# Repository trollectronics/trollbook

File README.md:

# Trollbook
*Homebrew 68040 palmtop computer* (http://h4xxel.org/electronics/trollbook/)

This is a work-in-progress palmtop (ish) sized clamshell laptop that we've been
working on for a while.

In its current state, it boots up into a BIOS menu capable of doing
a few simple things like browsing a FAT formatted SD-card, flashing its bootrom
from SD-card and excuting programs from SD-card.
One of the included demo programs can play .MOD music files from SD card.

The entire setup uses about 4.3 Watts while running, including
display and backlight.

The hardware specs as of now can be summed up as following:

 - Motorola 68040FE33V CPU, running at 33 MHz
 - Altera Flex10KA FPGA for glue logic and peripherals (video, uart, spi, audio etc.)
 - Atmel attiny48 for scanning keyboard matrix and mouse, interfacing to I2C peripherals
 - 512 kB of SRAM (used for frame buffer, sound buffer and stage 2 BIOS code)
 - 64 MB of SDRAM
 - 800x480 resolution 7" TFT display, driven at 256 colors (from a 16-bpp palette)
 - Stereo audio DAC, 8 bit/channel, samplerate of 48 kHz
 - SD card interface over SPI
 - On-board SPI Flash ROM (512 kB) for BIOS code
 - 7.4 V, 2.2 Ah battery pack with custom balancing circuitry (which sucks)

The (blue) mainboard is a 10x10 cm 4-layer board, designed by us and manufactured by a Chinese PCB fab.
The larger upper board is a CNC milled peripheral board sporting the keyboard, mouse, IO ports and power supplies.
We desperately need to make a proper case...

## This repository
This repository contains the following:
 - Hardware schematics and layout (kicad)
   - Current Rev 2 motherboard
   - Peripheral board
 - VHDL code for the glue logic/peripheral controller FPGA
 - Source code
   - Stage 1 boot, resides in a small ROM block in the FPGA
   - Stage 2 bios, resides in the large SPI rom
   - Demo code for feature testing/demonstration

## Companion projects
The following projects have been developed for the system:
 - The m68k-emu system emulator (https://github.com/slaeshjag/m68k-emu)
 - The trollos operating system (https://github.com/h4xxel/trollos)

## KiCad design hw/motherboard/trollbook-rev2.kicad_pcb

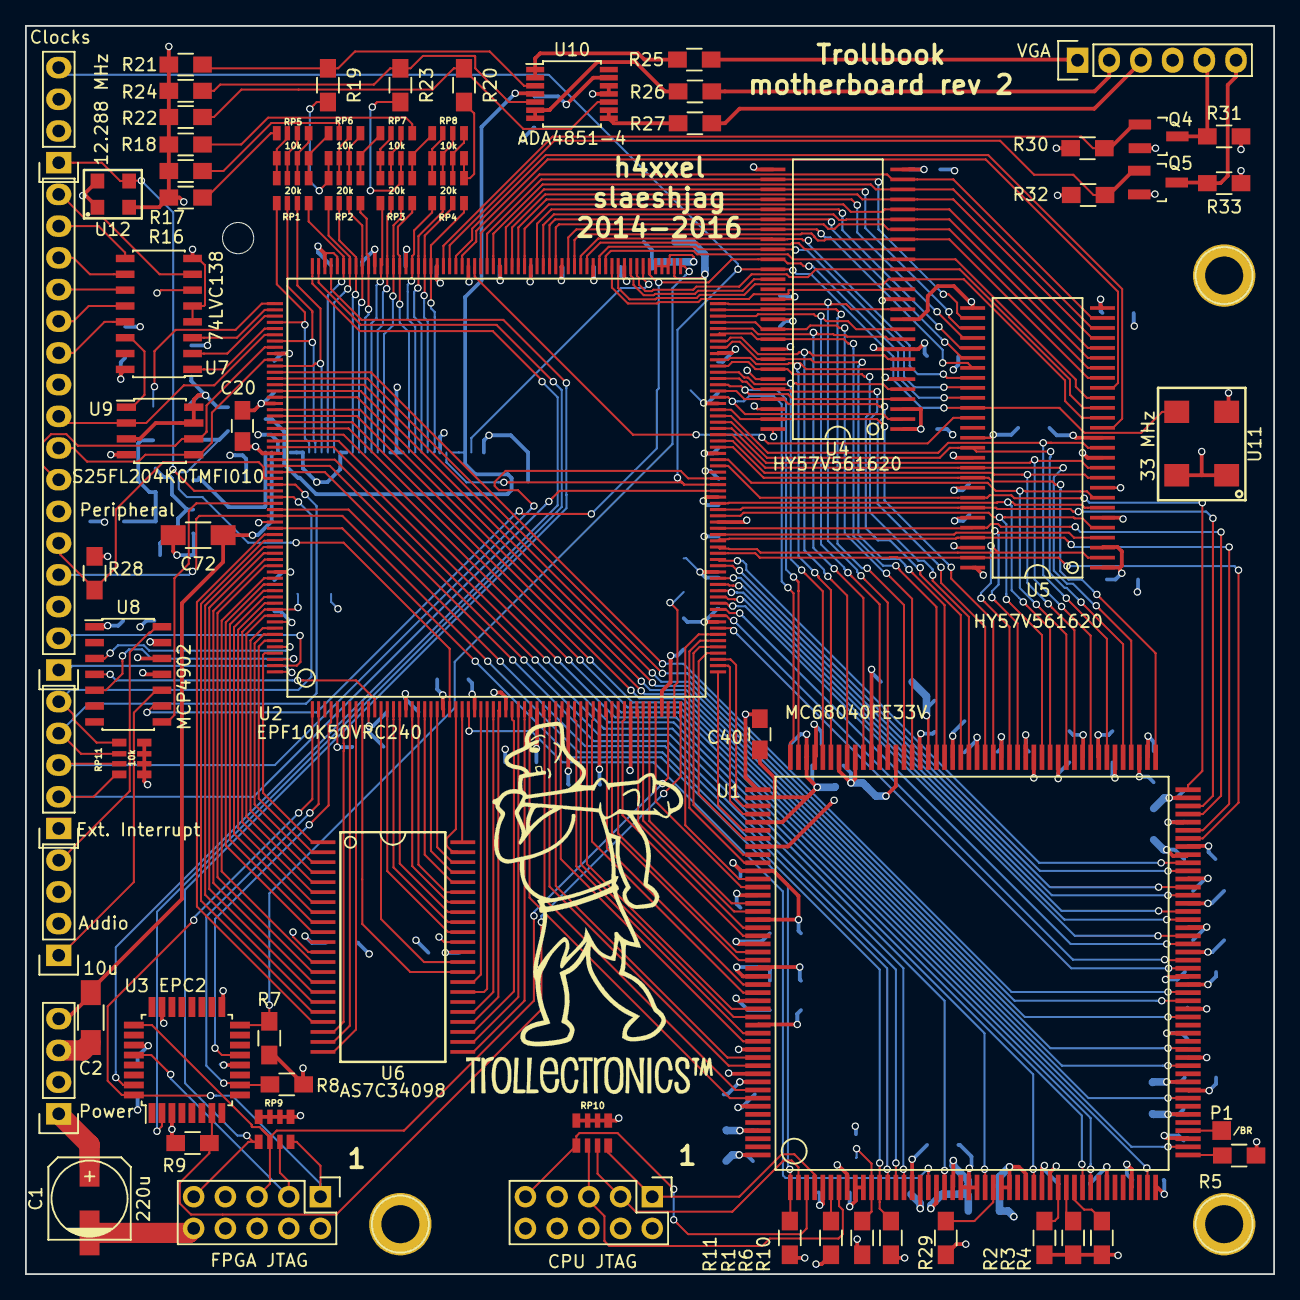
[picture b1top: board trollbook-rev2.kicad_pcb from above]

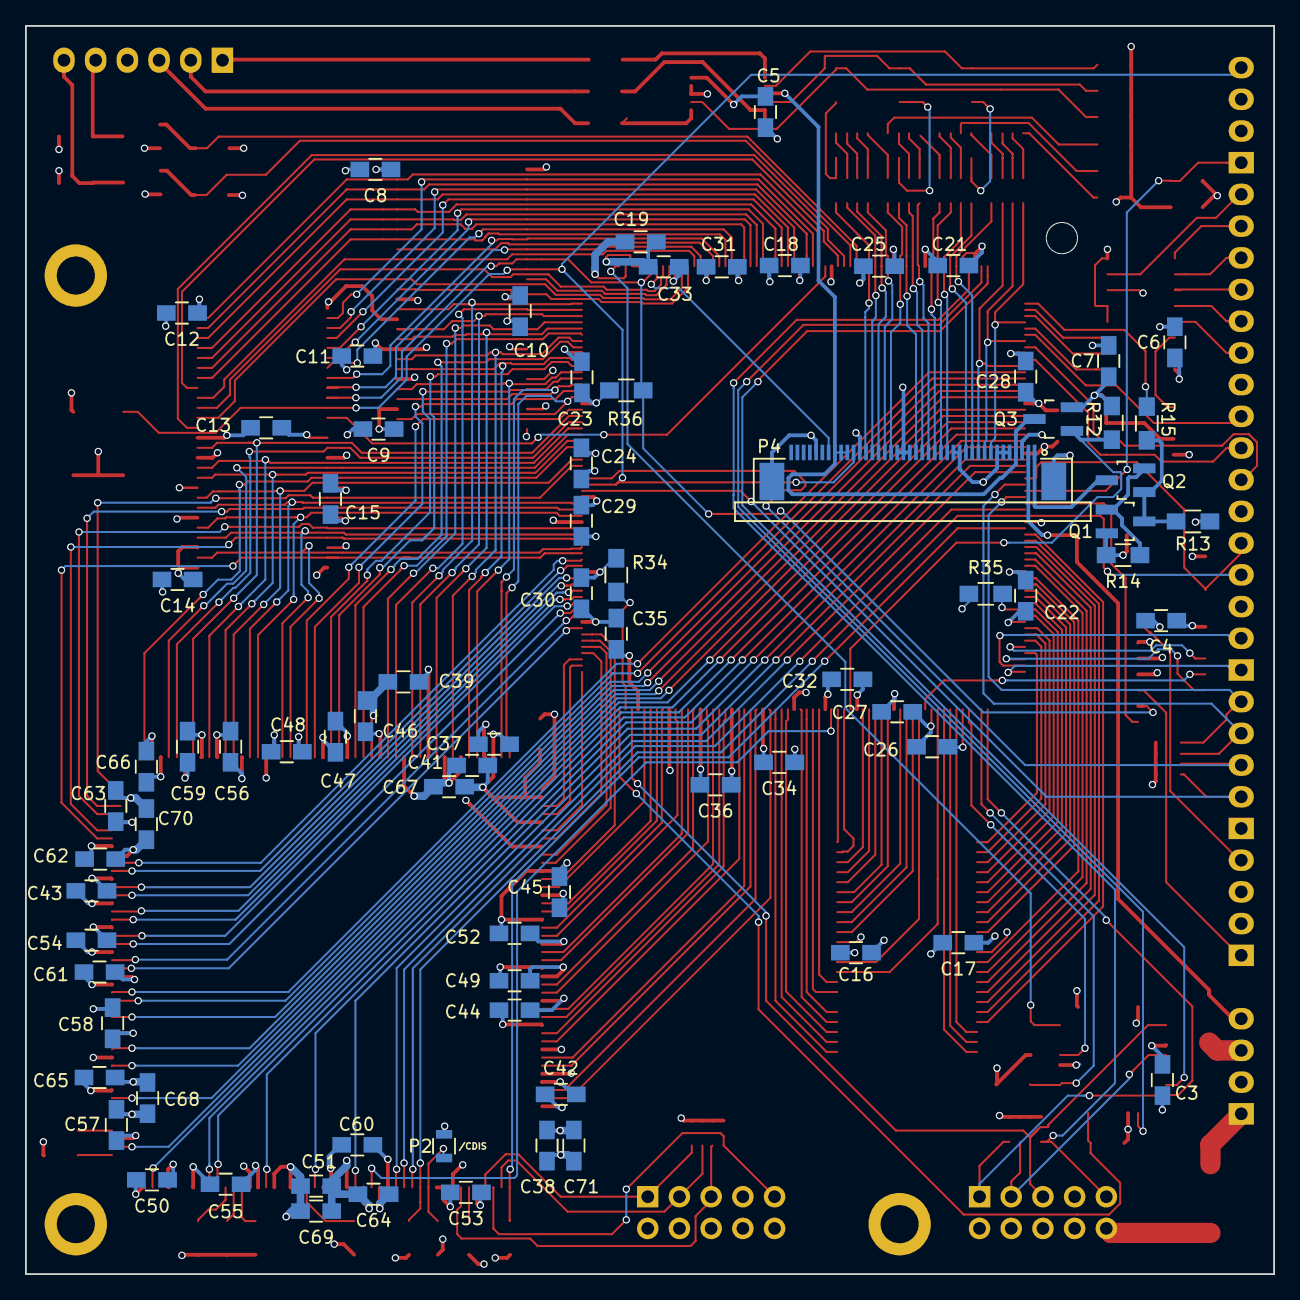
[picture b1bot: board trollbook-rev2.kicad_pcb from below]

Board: 4 copper layers, 100.0 x 100.0 mm, 147 parts (79 on the bottom side), 258 nets.

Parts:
C1: 220u; c_elec_6.3x7.7
C2: 10u; C_1206_HandSoldering
C3, C4, C5, C6, C7, C8, C9, C10, C11, C12, C13, C14, C15, C16, C17, C18, C19, C20, C21, C22, C23, C24, C25, C26, C27, C28, C29, C30, C31, C32, C33, C34, C35, C36, C67, C68, C69, C70, C71: 100n; C_0805_HandSoldering
C37, C38, C39, C40, C41, C42, C43, C44, C45, C46, C47, C48, C49, C50, C51, C52, C53, C54, C55, C56, C57, C58, C59, C60, C61, C62, C63, C64, C65, C66: 10n; C_0805_HandSoldering
C72: 1u; C_1206_HandSoldering
CON1: FPGA JTAG; Pin_Header_Straight_2x05
CON2: CPU JTAG; Pin_Header_Straight_2x05
P1: /BR; Measurement_Point_Square-SMD-Pad_Small
P2: /CDIS; R_0805
P3: Audio; Pin_Header_Straight_1x04
P4: ER-CON40HT-1
P5: Power; Pin_Header_Straight_1x04
P6: Peripheral; Pin_Header_Straight_1x16
P7: VGA; Pin_Header_Straight_1x06
P8: Clocks; Pin_Header_Straight_1x04
P9: Ext. Interrupt; Pin_Header_Straight_1x05
Q1, Q2, Q4, Q5: 2N7002E; SOT-23_Handsoldering
Q3: DMP3030SN-7; SOT-23_Handsoldering
R1, R10, R11, R15, R29, R30, R31, R32, R33: R; R_0805_HandSoldering
R2, R3, R4, R5, R6, R12, R16, R17, R18, R34, R35, R36: 10k; R_0805_HandSoldering
R7, R8, R9, R28: 1k; R_0805_HandSoldering
R13: 470k; R_0805_HandSoldering
R14: 20R; R_0805_HandSoldering
R19, R20, R23: 560k; R_0805_HandSoldering
R21, R22, R24: 180k; R_0805_HandSoldering
R25, R26, R27: 75; R_0805_HandSoldering
RP1, RP2, RP3, RP4: 20k; RPACK8_SMD
RP5, RP6, RP7, RP8, RP9, RP10, RP11: 10k; RPACK8_SMD
U1: MC68040FE33V; QFP-184
U2: EPF10K50VRC240; RQFP-240
U3: EPC2; TQFP-32_7x7mm_Pitch0.8mm
U4, U5: HY57V561620; TSOP54
U6: AS7C34098; TSOP44
U7: 74LVC138; SOIC-16_3.9x9.9mm_Pitch1.27mm
U8: MCP4902; SOIC-14_3.9x8.7mm_Pitch1.27mm
U9: S25FL204K0TMFI010; SOIC-8_3.9x4.9mm_Pitch1.27mm
U10: ADA4851-4; TSSOP-14_4.4x5mm_Pitch0.65mm
U11: 33 MHz; OSC-VCC1-B3B
U12: 12.288 MHz; OSC-ASFLMB

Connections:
+3V3: C1.1, C3.1, C4.1, C5.1, C6.1, C7.1, C8.1, C9.1, C10.1, C11.1, C12.1, C13.1, C14.1, C15.1, C16.1, C17.1, C18.1, C19.1, C20.1, C21.1, C22.1, C23.2, C24.2, C25.2, C26.2, C27.2, C28.1, C29.1, C30.1, C31.1, C32.1, C33.2, C34.2, C35.2, C36.2, C37.1, C38.1, C39.1, C40.1, C41.1, C42.2, C43.2, C44.2, C45.2, C46.2, C47.1, C48.1, C49.1, C50.1, C51.1, C52.2, C53.2, C54.2, C55.2, C56.2, C57.1, C58.1, C59.1, C60.1, C61.1, C62.2, C63.2, C64.2, C65.2, C66.2, C67.1, C68.1, C69.1, C70.1, C71.1, CON1.4, CON2.4, P5.1, Q3.2, R5.1, R6.2, R7.1, R8.1, R9.1, R11.1, R15.1, R29.1, R30.2, R31.2, R32.2, R33.2, R34.1, R35.1, RP9.1, RP9.2, RP9.3, RP9.4, RP10.1, RP10.2, RP10.3, RP10.4, RP11.1, RP11.2, RP11.3, RP11.4, U1.9, U1.10, U1.16, U1.19, U1.21, U1.32, U1.43, U1.49, U1.56, U1.62, U1.69, U1.75, U1.81, U1.84, U1.88, U1.94, U1.100, U1.102, U1.109, U1.115, U1.122, U1.128, U1.136, U1.140, U1.143, U1.149, U1.155, U1.161, U1.168, U1.175, U1.181, U2.5, U2.16, U2.27, U2.37, U2.47, U2.57, U2.77, U2.89, U2.96, U2.112, U2.122, U2.130, U2.140, U2.150, U2.160, U2.170, U2.189, U2.205, U2.224, U3.3, U3.17, U3.23, U3.27, U4.1, U4.3, U4.9, U4.14, U4.27, U4.43, U4.49, U5.1, U5.3, U5.9, U5.14, U5.27, U5.43, U5.49, U6.11, U6.33, U7.6, U7.16, U8.1, U8.11, U8.13, U9.3, U9.7, U9.8, U10.13, U11.1, U11.4, U12.1, U12.4
/A0: U1.70, U2.68
/A1: U1.71, U2.70
/A2: U1.73, U2.71
/A3: U1.74, U2.72
/A4: U1.76, U2.73
/A5: U1.77, U2.74
/A6: U1.79, U2.75
/A7: U1.80, U2.76
/A8: U1.82, U2.78
/A9: U1.83, U2.79
/A10: U1.173, U2.39
/A11: U1.172, U2.40
/A12: U1.170, U2.41
/A13: U1.169, U2.43
/A14: U1.167, U2.44
/A15: U1.166, U2.45
/A16: U1.164, U2.46
/A17: U1.163, U2.48
/A18: U1.160, U2.49
/A19: U1.159, U2.50
/A20: U1.157, U2.51
/A21: U1.156, U2.53
/A22: U1.154, U2.54
/A23: U1.153, U2.55
/A24: U1.151, U2.56
/A25: U1.150, U2.67
/A26: U1.148, U2.66
/A27: U1.147, U2.65
/A28: U1.145, U2.64
/A29: U1.144, U2.61
/A30: U1.142, U2.62
/A31: U1.141, U2.63
/AUDIOL: P3.4, U8.14
/AUDIOR: P3.1, U8.10
/CLK12: P8.1, U2.211, U12.3
/CLK33: P4.30, P8.4, U2.91, U4.38, U5.38, U11.3
/CONF_CLK: U2.179, U3.2
/CONF_CS: R8.2, U2.2, U3.10
/CONF_DATA: U2.180, U3.31
/CONF_INIT: R7.2, U2.121, U3.16
/CONF_OE: R9.2, U2.60, U3.7
/CONF_TDO: CON1.3, RP9.7, U3.28
/CPUBB: R5.2, U1.47
/CPUBG: R4.2, U1.36
/CPUBR: P1.1, U1.50
/CPUCDIS: P2.1, R6.1, U1.11
/CPUCLK: U1.18, U2.26
/CPUIPL0: U1.15, U2.207
/CPUIPL1: U1.14, U2.208
/CPUIPL2: U1.13, U2.214
/CPULFO: U1.20, U2.206
/CPULOC: R1.2, U1.6
/CPURSTI: P6.4, R10.2, U1.12, U2.215
/CPURSTO: R11.2, U1.1, U2.217
/CPURW: U1.58, U2.196
/CPUSC0: R2.2, U1.34
/CPUSC1: R3.2, U1.35
/CPUSCD: U1.25, U2.204
/CPUSIZ0: U1.60, U2.195
/CPUSIZ1: U1.54, U2.198
/CPUTA: U1.38, U2.201
/CPUTBI: U1.31, U2.203
/CPUTCK: CON2.1, RP10.8, U1.4
/CPUTDI: CON2.9, RP10.5, U1.3
/CPUTDO: CON2.3, RP10.7, U1.2
/CPUTEA: U1.37, U2.202
/CPUTIP: U1.45, U2.200
/CPUTM0: U1.64, U2.194
/CPUTM1: U1.66, U2.193
/CPUTM2: U1.67, U2.192
/CPUTMS: CON2.5, RP10.6, U1.7
/CPUTP: U1.48, U2.199
/CPUTT0: U1.177, U2.36
/CPUTT1: U1.176, U2.38
/D0: U1.138, U2.105, U4.2
/D1: U1.137, U2.107, U4.4
/D2: U1.134, U2.109, U4.5
/D3: U1.133, U2.111, U4.7
/D4: U1.131, U2.114, U4.8
/D5: U1.129, U2.116, U4.10
/D6: U1.127, U2.118, U4.11
/D7: U1.126, U2.120, U4.13
/D8: U1.124, U2.119, U4.42
/D9: U1.123, U2.117, U4.44
/D10: U1.120, U2.115, U4.45
/D11: U1.119, U2.113, U4.47
/D12: U1.117, U2.110, U4.48
/D13: U1.116, U2.108, U4.50
/D14: U1.114, U2.106, U4.51
/D15: U1.113, U2.103, U4.53
/D16: U1.111, U2.81, U5.2
/D17: U1.110, U2.83, U5.4
/D18: U1.107, U2.86, U5.5
/D19: U1.106, U2.88, U5.7
/D20: U1.104, U2.95, U5.8
/D21: U1.103, U2.98, U5.10
/D22: U1.101, U2.100, U5.11
/D23: U1.99, U2.102, U5.13
/D24: U1.97, U2.101, U5.42
/D25: U1.96, U2.99, U5.44
/D26: U1.93, U2.97, U5.45
/D27: U1.92, U2.94, U5.47
/D28: U1.90, U2.87, U5.48
/D29: U1.89, U2.84, U5.50
/D30: U1.87, U2.82, U5.51
/D31: U1.86, U2.80, U5.53
/EXTINT0: P9.2, RP11.8, U2.90
/EXTINT1: P9.3, RP11.7, U2.92
/EXTINT2: P9.4, RP11.6, U2.210
/EXTINT3: P9.5, RP11.5, U2.212
/FPGA_TCK: CON1.1, RP9.8, U2.1, U3.32
/FPGA_TDI: CON1.9, RP9.5, U2.177
/FPGA_TDO: U2.4, U3.13
/FPGA_TMS: CON1.5, RP9.6, U2.58, U3.25
/LLA1: U2.237, U6.1
/LLA2: U2.235, U6.2
/LLA3: U2.234, U6.3
/LLA4: U2.233, U6.4
/LLA5: U2.231, U6.5
/LLA6: U2.219, U6.18
/LLA7: U2.218, U6.19
/LLA8: U2.6, U6.20
/LLA9: U2.7, U6.21
/LLA10: U2.8, U6.22
/LLA11: U2.35, U6.23
/LLA12: U2.34, U6.24
/LLA13: U2.33, U6.25
/LLA14: U2.31, U6.26
/LLA15: U2.30, U6.27
/LLA16: U2.21, U6.42
/LLA17: U2.24, U6.43
/LLA18: U2.25, U6.44
/LLCE: R35.2, U2.230, U6.6
/LLD0: U2.229, U6.7
/LLD1: U2.228, U6.8
/LLD2: U2.227, U6.9
/LLD3: U2.226, U6.10
/LLD4: U2.225, U6.13
/LLD5: U2.223, U6.14
/LLD6: U2.222, U6.15
/LLD7: U2.221, U6.16
/LLD8: U2.29, U6.29
/LLD9: U2.28, U6.30
/LLD10: U2.9, U6.31
/LLD11: U2.12, U6.32
/LLD12: U2.13, U6.35
/LLD13: U2.14, U6.36
/LLD14: U2.15, U6.37
/LLD15: U2.17, U6.38
/LLLB: U2.18, U6.39
/LLOE: U2.20, U6.41
/LLUB: U2.19, U6.40
/LLWE: U2.220, U6.17
/PWRON_RESET: P6.5, R28.1, U2.209
/RAM0CS: U2.136, U4.19
/RAM0LDQM: U2.132, U4.15
/RAM0UDQM: U2.129, U4.39
/RAM1CS: U2.156, U5.19
/RAM1LDQM: U2.157, U5.15
/RAM1UDQM: U2.154, U5.39
/RAMA0: U2.146, U4.23, U5.23
/RAMA1: U2.148, U4.24, U5.24
/RAMA2: U2.151, U4.25, U5.25
/RAMA3: U2.153, U4.26, U5.26
/RAMA4: U2.152, U4.29, U5.29
/RAMA5: U2.149, U4.30, U5.30
/RAMA6: U2.147, U4.31, U5.31
/RAMA7: U2.144, U4.32, U5.32
/RAMA8: U2.142, U4.33, U5.33
/RAMA9: U2.139, U4.34, U5.34
/RAMA10: U2.143, U4.22, U5.22
/RAMA11: U2.137, U4.35, U5.35
/RAMA12: U2.134, U4.36, U5.36
/RAMB0: U2.138, U4.20, U5.20
/RAMB1: U2.141, U4.21, U5.21
/RAMCAS: U2.128, U4.17, U5.17
/RAMCKE: R36.1, U2.126, U4.37, U5.37, U8.9
/RAMRAS: U2.133, U4.18, U5.18
/RAMWE: U2.131, U4.16, U5.16
/SNDSYNC: U2.213, U8.8
/SPI0CLK: P6.7, U2.188, U9.6
/SPI0MISO: P6.9, U2.186, U9.2
/SPI0MOSI: P6.8, U2.190, U9.5
/SPI0SS1: U7.14, U9.1
/SPI0SS2: P6.11, U7.13
/SPI0SS3: P6.12, U7.12
/SPI0SS4: P6.13, U7.11
/SPI0SS5: P6.14, U7.10
/SPI0SS6: P6.15, U7.9
/SPI0SS7: P6.16, U7.7
/SPI0SSBIT0: U2.185, U7.1
/SPI0SSBIT1: U2.183, U7.2
/SPI0SSBIT2: U2.182, U7.3
/SPI1CLK: U2.11, U8.4
/SPI1MOSI: U2.238, U8.5
/SPI1SS: U2.236, U8.3
/UARTRX: P6.1, U2.240
/UARTTX: P6.2, U2.239
/VGAB0: P4.24, RP3.4, U2.166
/VGAB1: P4.25, RP4.1, U2.164
/VGAB2: P4.26, RP4.2, U2.163
/VGAB3: P4.27, RP4.3, U2.162
/VGAB4: P4.28, RP4.4, U2.161
/VGADEN: P4.34, U2.127
/VGADISP: P4.4, P4.31, P4.32, P4.33, Q3.3, U10.4
/VGAG0: P4.15, RP2.2, U2.173
/VGAG1: P4.16, RP2.3, U2.172
/VGAG2: P4.17, RP2.4, U2.171
/VGAG3: P4.18, RP3.1, U2.169
/VGAG4: P4.19, RP3.2, U2.168
/VGAG5: P4.20, RP3.3, U2.167
/VGAHSYNC: Q4.1, R30.1, U2.159
/VGALED_ANODE: C2.1, C72.1, P4.2, P5.4
/VGALED_CATHODE: P4.1, Q2.3
/VGALED_PWM: R12.2, U2.181
/VGAPWR: Q3.1, R15.2, U2.23
/VGAR0: P4.8, RP1.1, U2.184
/VGAR1: P4.9, RP1.2, U2.187
/VGAR2: P4.10, RP1.3, U2.191
/VGAR3: P4.11, RP1.4, U2.175
/VGAR4: P4.12, RP2.1, U2.174
/VGAVSYNC: Q5.1, R32.1, U2.158
GND: C1.2, C2.2, C3.2, C4.2, C5.2, C6.2, C7.2, C8.2, C9.2, C10.2, C11.2, C12.2, C13.2, C14.2, C15.2, C16.2, C17.2, C18.2, C19.2, C20.2, C21.2, C22.2, C23.1, C24.1, C25.1, C26.1, C27.1, C28.2, C29.2, C30.2, C31.2, C32.2, C33.1, C34.1, C35.1, C36.1, C37.2, C38.2, C39.2, C40.2, C41.2, C42.1, C43.1, C44.1, C45.1, C46.1, C47.2, C48.2, C49.2, C50.2, C51.2, C52.1, C53.1, C54.1, C55.1, C56.1, C57.2, C58.2, C59.2, C60.2, C61.2, C62.1, C63.1, C64.1, C65.1, C66.1, C67.2, C68.2, C69.2, C70.2, C71.2, C72.2, CON1.2, CON1.10, CON2.2, CON2.10, P2.2, P3.2, P3.3, P4.3, P4.5, P4.6, P4.7, P4.13, P4.14, P4.21, P4.22, P4.23, P4.29, P4.36, P4.GND, P5.2, P5.3, P6.3, P6.6, P6.10, P7.4, P8.2, P8.3, P9.1, Q1.2, Q4.2, Q5.2, R1.1, R2.1, R3.1, R4.1, R10.1, R13.2, R14.2, R16.1, R17.1, R18.1, R21.2, R22.2, R24.2, R28.2, R36.2, U1.5, U1.8, U1.17, U1.22, U1.23, U1.24, U1.27, U1.28, U1.30, U1.33, U1.40, U1.46, U1.52, U1.55, U1.59, U1.65, U1.68, U1.72, U1.78, U1.85, U1.91, U1.95, U1.98, U1.105, U1.108, U1.112, U1.118, U1.121, U1.125, U1.130, U1.132, U1.135, U1.139, U1.146, U1.152, U1.158, U1.162, U1.165, U1.171, U1.174, U1.178, U1.184, U2.10, U2.22, U2.32, U2.42, U2.52, U2.69, U2.85, U2.93, U2.104, U2.123, U2.124, U2.125, U2.135, U2.145, U2.155, U2.165, U2.176, U2.178, U2.197, U2.216, U2.232, U3.12, U4.6, U4.12, U4.28, U4.41, U4.46, U4.52, U4.54, U5.6, U5.12, U5.28, U5.41, U5.46, U5.52, U5.54, U6.12, U6.34, U7.4, U7.5, U7.8, U8.12, U9.4, U10.11, U10.12, U11.2, U12.2
unnamed: P7.1, R25.1
unnamed: P7.2, R26.1
unnamed: P7.3, R27.1
unnamed: P7.5, Q4.3, R31.1
unnamed: P7.6, Q5.3, R33.1
unnamed: Q1.1, Q2.2, R14.1
unnamed: Q1.3, Q2.1, R12.1, R13.1
unnamed: R16.2, RP5.8
unnamed: R17.2, RP6.7
unnamed: R18.2, RP7.5
unnamed: R19.1, R21.1, U10.3
unnamed: R19.2, RP2.8, RP6.1
unnamed: R20.1, R22.1, U10.10
unnamed: R20.2, RP4.5, RP8.4
unnamed: R23.1, R24.1, U10.5
unnamed: R23.2, RP3.6, RP7.3
unnamed: R25.2, U10.1, U10.2
unnamed: R26.2, U10.6, U10.7
unnamed: R27.2, U10.8, U10.9
unnamed: R29.2, U1.26
unnamed: R34.2, U2.59
unnamed: RP1.5, RP5.4, RP6.8
unnamed: RP1.6, RP5.3, RP5.5
unnamed: RP1.7, RP5.2, RP5.6
unnamed: RP1.8, RP5.1, RP5.7
unnamed: RP2.5, RP6.4, RP7.8
unnamed: RP2.6, RP6.3, RP6.5
unnamed: RP2.7, RP6.2, RP6.6
unnamed: RP3.5, RP7.4, RP8.8
unnamed: RP3.7, RP7.2, RP7.6
unnamed: RP3.8, RP7.1, RP7.7
unnamed: RP4.6, RP8.3, RP8.5
unnamed: RP4.7, RP8.2, RP8.6
unnamed: RP4.8, RP8.1, RP8.7

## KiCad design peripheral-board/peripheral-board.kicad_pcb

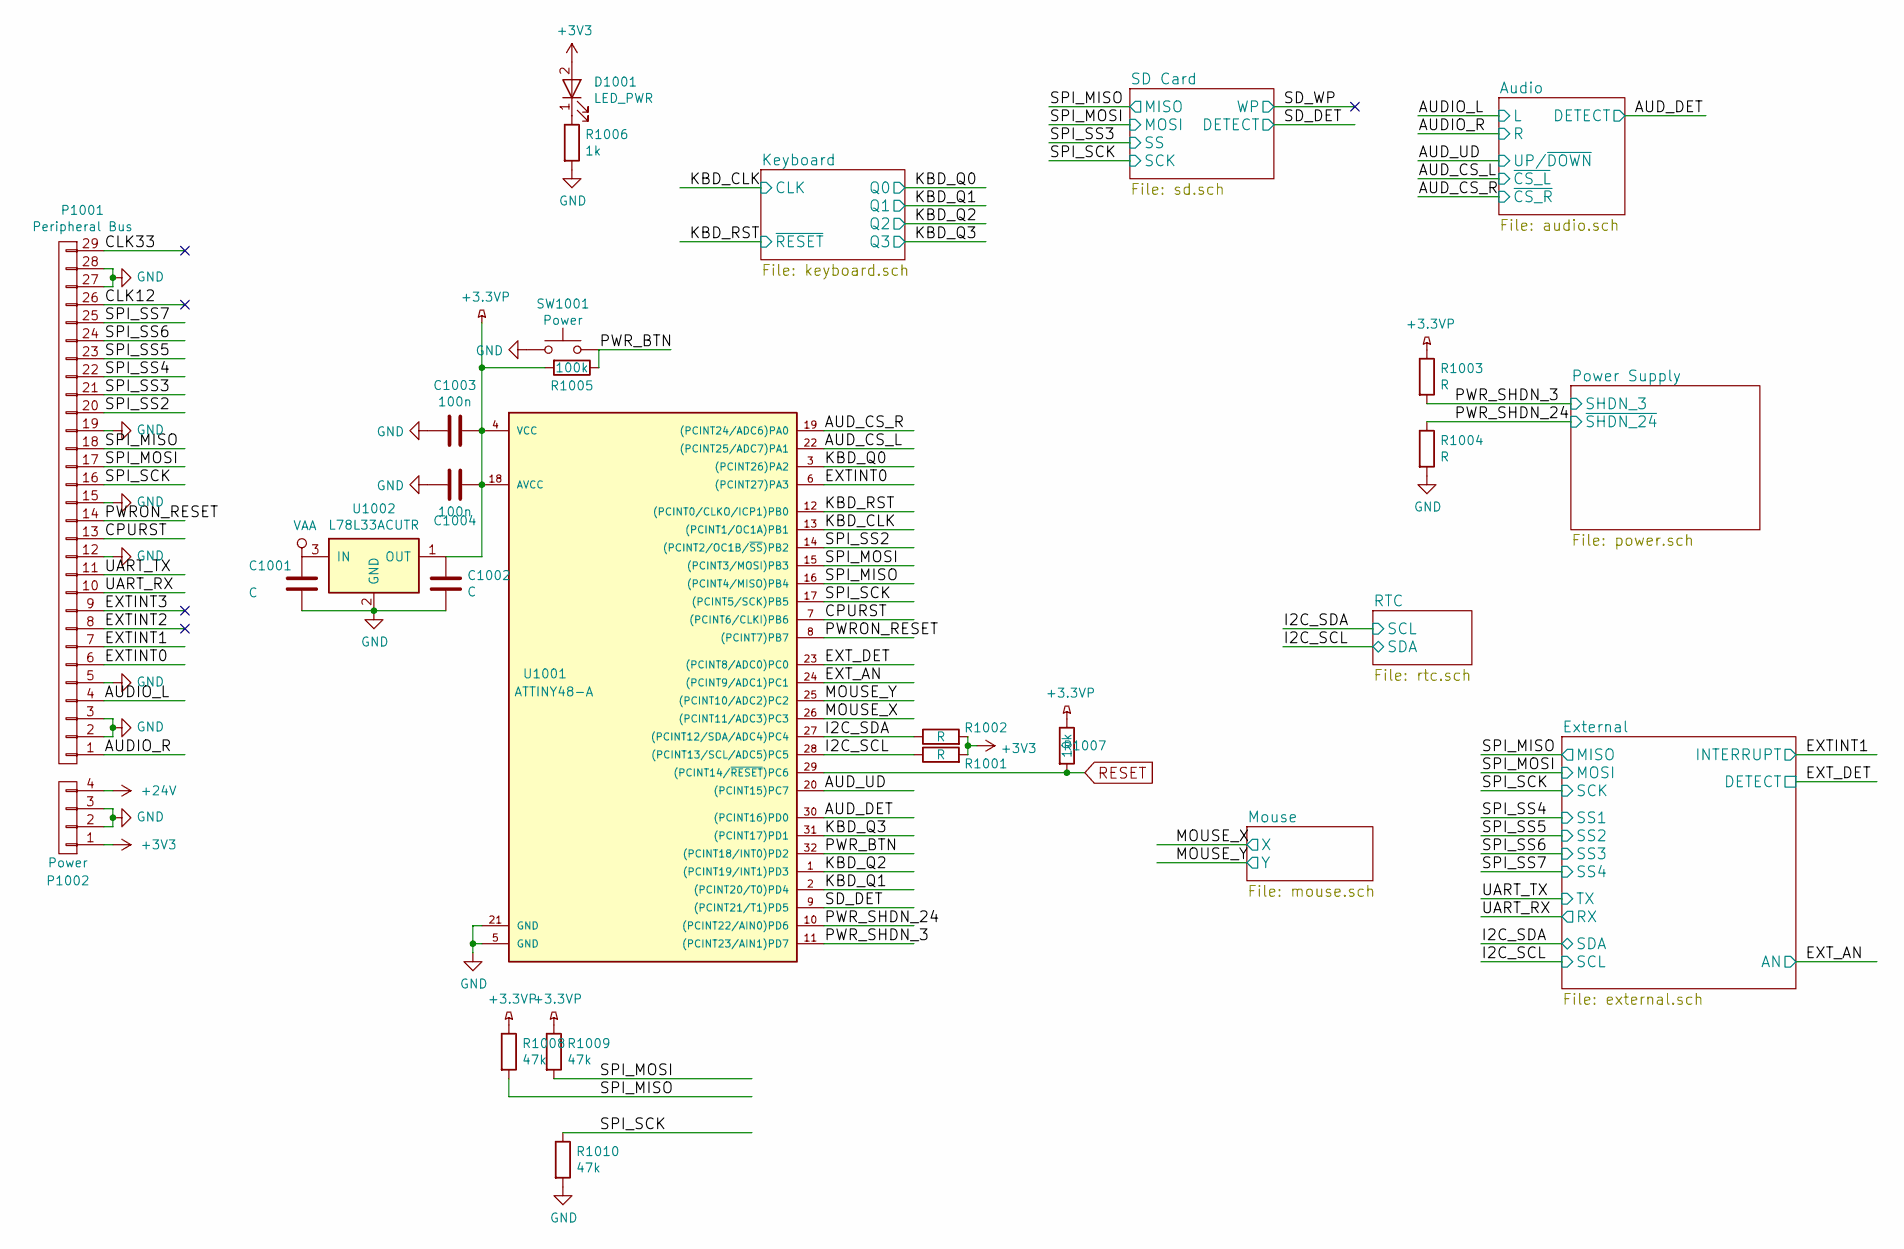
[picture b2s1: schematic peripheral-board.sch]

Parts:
C1001, C1002: C; C_0805
C1003, C1004: 100n; C_0805
D1001: LED_PWR; LED-3MM
P1001: Peripheral Bus; Socket_Strip_Straight_1x29
P1002: Power; Socket_Strip_Straight_1x04
R1001, R1002, R1003, R1004: R; R_0805
R1005: 100k; R_0805
R1006: 1k; R_0805
R1007: 10k; R_0805
R1008, R1009, R1010: 47k; R_0805
SW1001: Power; SMD-TACT-5.2x5.2x2mm
U1001: ATTINY48-A; TQFP-32_7x7mm_Pitch0.8mm
U1002: L78L33ACUTR; SOT89-3_Housing

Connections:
+3.3VP: C1002.1, C1003.1, C1004.1, R1003.1, R1005.2, R1007.1, R1008.1, R1009.1, U1001.4 (VCC), U1001.18 (AVCC), U1002.1 (OUT); also elsewhere on the board
+3V3: D1001.2 (A), P1002.1, R1001.2, R1002.2; also elsewhere on the board
+24V: P1002.4; also elsewhere on the board
/AUDIO_L: P1001.4; also elsewhere on the board
/AUDIO_R: P1001.1; also elsewhere on the board
/AUD_CS_L: U1001.22 ((PCINT25/ADC7)PA1); also elsewhere on the board
/AUD_CS_R: U1001.19 ((PCINT24/ADC6)PA0); also elsewhere on the board
/AUD_DET: U1001.30 ((PCINT16)PD0); also elsewhere on the board
/AUD_UD: U1001.20 ((PCINT15)PC7); also elsewhere on the board
/CLK12: P1001.26
/CLK33: P1001.29
/CPURST: P1001.13, U1001.7 ((PCINT6/CLKI)PB6)
/EXTINT0: P1001.6, U1001.6 ((PCINT27)PA3)
/EXTINT1: P1001.7; also elsewhere on the board
/EXTINT2: P1001.8
/EXTINT3: P1001.9
/EXT_AN: U1001.24 ((PCINT9/ADC1)PC1); also elsewhere on the board
/EXT_DET: U1001.23 ((PCINT8/ADC0)PC0); also elsewhere on the board
/I2C_SCL: R1001.1, U1001.28 ((PCINT13/SCL/ADC5)PC5); also elsewhere on the board
/I2C_SDA: R1002.1, U1001.27 ((PCINT12/SDA/ADC4)PC4); also elsewhere on the board
/KBD_CLK: U1001.13 ((PCINT1/OC1A)PB1); also elsewhere on the board
/KBD_Q0: U1001.3 ((PCINT26)PA2); also elsewhere on the board
/KBD_Q1: U1001.2 ((PCINT20/T0)PD4); also elsewhere on the board
/KBD_Q2: U1001.1 ((PCINT19/INT1)PD3); also elsewhere on the board
/KBD_Q3: U1001.31 ((PCINT17)PD1); also elsewhere on the board
/KBD_RST: U1001.12 ((PCINT0/CLKO/ICP1)PB0); also elsewhere on the board
/MOUSE_X: U1001.26 ((PCINT11/ADC3)PC3); also elsewhere on the board
/MOUSE_Y: U1001.25 ((PCINT10/ADC2)PC2); also elsewhere on the board
/PWRON_RESET: P1001.14, U1001.8 ((PCINT7)PB7)
/PWR_BTN: R1005.1, SW1001.2, U1001.32 ((PCINT18/INT0)PD2)
/PWR_SHDN_3: R1003.2, U1001.11 ((PCINT23/AIN1)PD7); also elsewhere on the board
/PWR_SHDN_24: R1004.1, U1001.10 ((PCINT22/AIN0)PD6); also elsewhere on the board
/SD_DET: U1001.9 ((PCINT21/T1)PD5); also elsewhere on the board
/SPI_MISO: P1001.18, R1008.2, U1001.16 ((PCINT4/MISO)PB4); also elsewhere on the board
/SPI_MOSI: P1001.17, R1009.2, U1001.15 ((PCINT3/MOSI)PB3); also elsewhere on the board
/SPI_SCK: P1001.16, R1010.1, U1001.17 ((PCINT5/SCK)PB5); also elsewhere on the board
/SPI_SS2: P1001.20, U1001.14 ((PCINT2/OC1B/~SS~)PB2)
/SPI_SS3: P1001.21; also elsewhere on the board
/SPI_SS4: P1001.22; also elsewhere on the board
/SPI_SS5: P1001.23; also elsewhere on the board
/SPI_SS6: P1001.24; also elsewhere on the board
/SPI_SS7: P1001.25; also elsewhere on the board
/UART_RX: P1001.10; also elsewhere on the board
/UART_TX: P1001.11; also elsewhere on the board
GND: C1001.2, C1002.2, C1003.2, C1004.2, P1001.2, P1001.3, P1001.5, P1001.12, P1001.15, P1001.19, P1001.27, P1001.28, P1002.2, P1002.3, R1004.2, R1006.2, R1010.2, SW1001.1, U1001.5 (GND), U1001.21 (GND), U1002.2 (GND); also elsewhere on the board
unnamed: D1001.1 (K), R1006.1
RESET: R1007.2, U1001.29 ((PCINT14/~RESET~)PC6); also elsewhere on the board
VAA: C1001.1, U1002.3 (IN); also elsewhere on the board

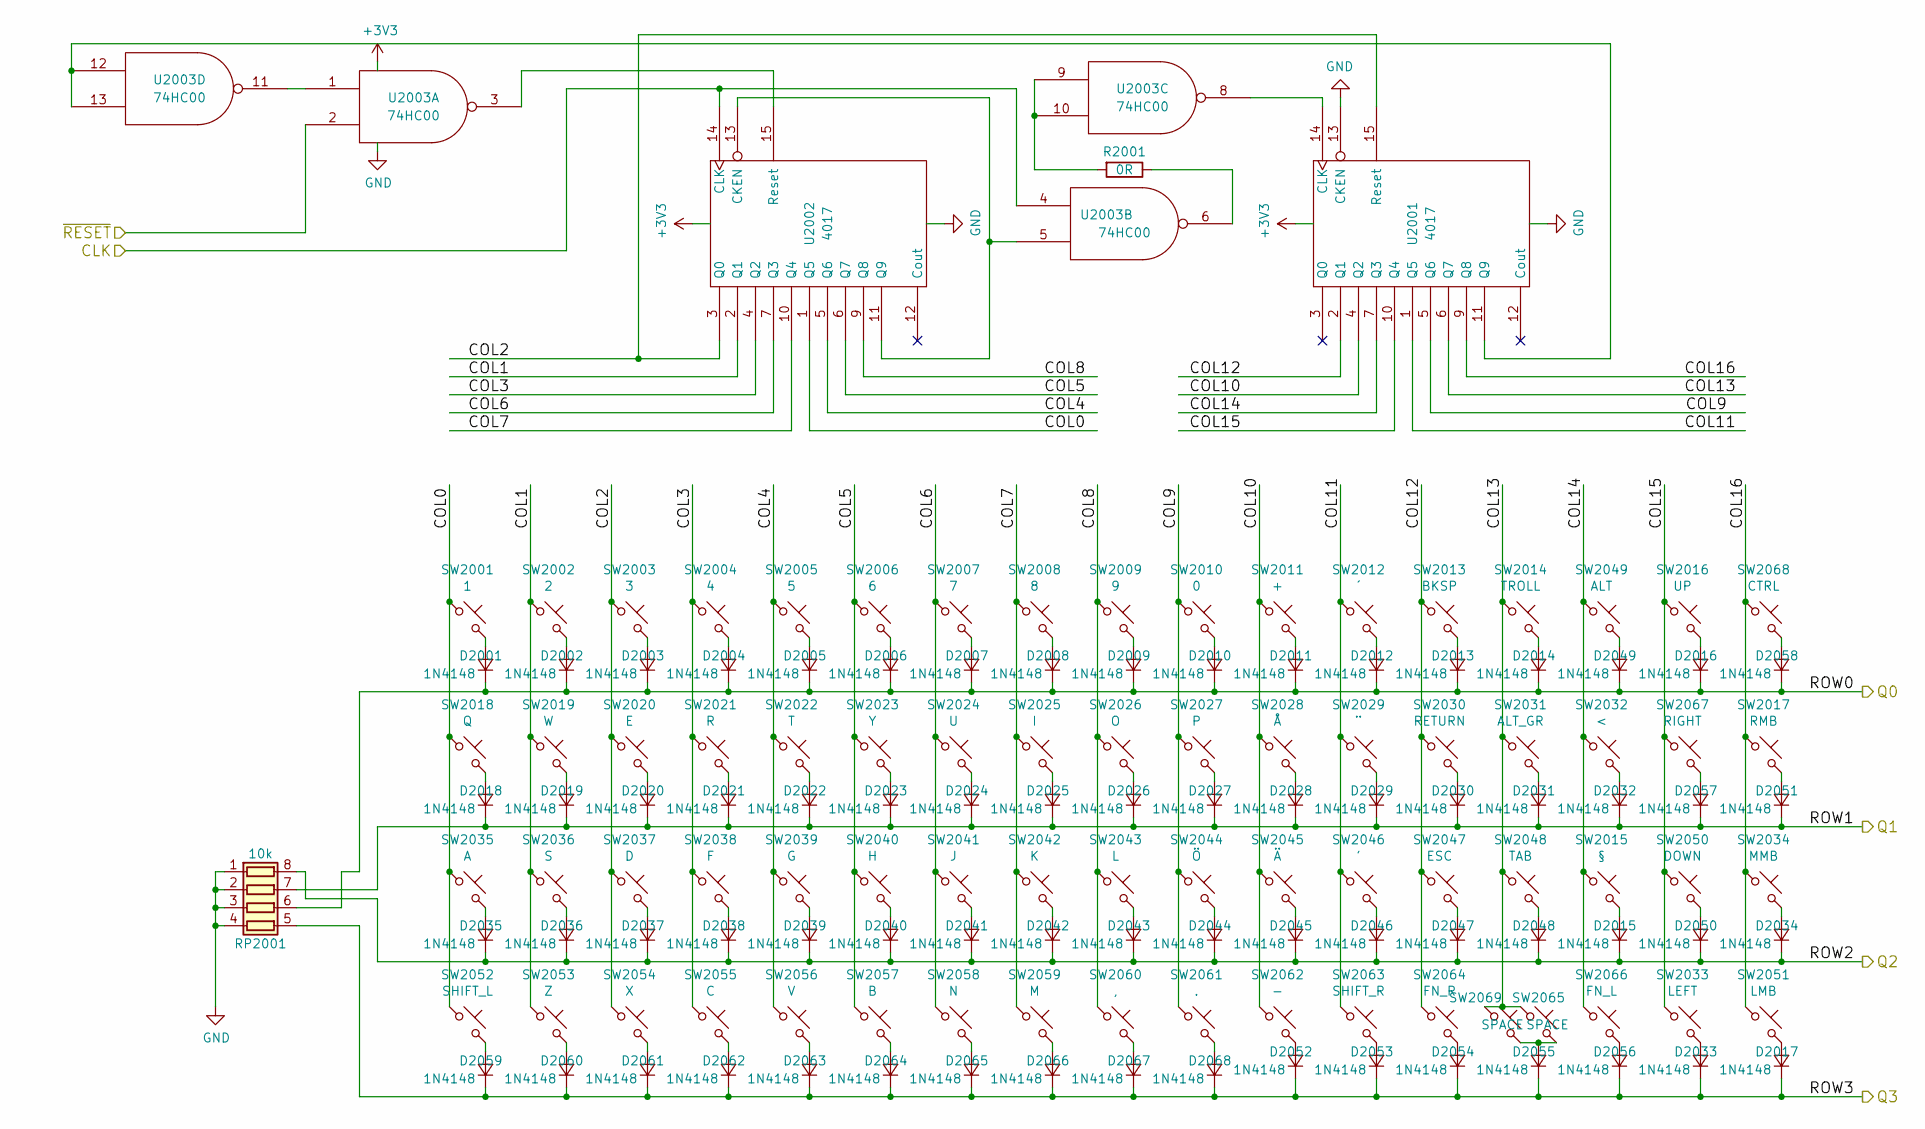
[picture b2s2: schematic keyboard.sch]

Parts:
D2001, D2002, D2003, D2004, D2005, D2006, D2007, D2008, D2009, D2010, D2011, D2012, D2013, D2014, D2015, D2016, D2017, D2018, D2019, D2020, D2021, D2022, D2023, D2024, D2025, D2026, D2027, D2028, D2029, D2030, D2031, D2032, D2033, D2034, D2035, D2036, D2037, D2038, D2039, D2040, D2041, D2042, D2043, D2044, D2045, D2046, D2047, D2048, D2049, D2050, D2051, D2052, D2053, D2054, D2055, D2056, D2057, D2058, D2059, D2060, D2061, D2062, D2063, D2064, D2065, D2066, D2067, D2068: 1N4148; D_MiniMELF_Standard
R2001: 0R; R_1206
RP2001: 10k; R_Cat16-4
SW2001: 1; SMD-TACT-5.2x5.2x2mm
SW2002: 2; SMD-TACT-5.2x5.2x2mm
SW2003: 3; SMD-TACT-5.2x5.2x2mm
SW2004: 4; SMD-TACT-5.2x5.2x2mm
SW2005: 5; SMD-TACT-5.2x5.2x2mm
SW2006: 6; SMD-TACT-5.2x5.2x2mm
SW2007: 7; SMD-TACT-5.2x5.2x2mm
SW2008: 8; SMD-TACT-5.2x5.2x2mm
SW2009: 9; SMD-TACT-5.2x5.2x2mm
SW2010: 0; SMD-TACT-5.2x5.2x2mm
SW2011: +; SMD-TACT-5.2x5.2x2mm
SW2012: ´; SMD-TACT-5.2x5.2x2mm
SW2013: BKSP; SMD-TACT-5.2x5.2x2mm
SW2014: TROLL; SMD-TACT-5.2x5.2x2mm
SW2015: §; SMD-TACT-5.2x5.2x2mm
SW2016: UP; SMD-TACT-5.2x5.2x2mm
SW2017: RMB; SMD-TACT-5.2x5.2x2mm
SW2018: Q; SMD-TACT-5.2x5.2x2mm
SW2019: W; SMD-TACT-5.2x5.2x2mm
SW2020: E; SMD-TACT-5.2x5.2x2mm
SW2021: R; SMD-TACT-5.2x5.2x2mm
SW2022: T; SMD-TACT-5.2x5.2x2mm
SW2023: Y; SMD-TACT-5.2x5.2x2mm
SW2024: U; SMD-TACT-5.2x5.2x2mm
SW2025: I; SMD-TACT-5.2x5.2x2mm
SW2026: O; SMD-TACT-5.2x5.2x2mm
SW2027: P; SMD-TACT-5.2x5.2x2mm
SW2028: Å; SMD-TACT-5.2x5.2x2mm
SW2029: ¨; SMD-TACT-5.2x5.2x2mm
SW2030: RETURN; SMD-TACT-5.2x5.2x2mm
SW2031: ALT_GR; SMD-TACT-5.2x5.2x2mm
SW2032: <; SMD-TACT-5.2x5.2x2mm
SW2033: LEFT; SMD-TACT-5.2x5.2x2mm
SW2034: MMB; SMD-TACT-5.2x5.2x2mm
SW2035: A; SMD-TACT-5.2x5.2x2mm
SW2036: S; SMD-TACT-5.2x5.2x2mm
SW2037: D; SMD-TACT-5.2x5.2x2mm
SW2038: F; SMD-TACT-5.2x5.2x2mm
SW2039: G; SMD-TACT-5.2x5.2x2mm
SW2040: H; SMD-TACT-5.2x5.2x2mm
SW2041: J; SMD-TACT-5.2x5.2x2mm
SW2042: K; SMD-TACT-5.2x5.2x2mm
SW2043: L; SMD-TACT-5.2x5.2x2mm
SW2044: Ö; SMD-TACT-5.2x5.2x2mm
SW2045: Ä; SMD-TACT-5.2x5.2x2mm
SW2046: '; SMD-TACT-5.2x5.2x2mm
SW2047: ESC; SMD-TACT-5.2x5.2x2mm
SW2048: TAB; SMD-TACT-5.2x5.2x2mm
SW2049: ALT; SMD-TACT-5.2x5.2x2mm
SW2050: DOWN; SMD-TACT-5.2x5.2x2mm
SW2051: LMB; SMD-TACT-5.2x5.2x2mm
SW2052: SHIFT_L; SMD-TACT-5.2x5.2x2mm
SW2053: Z; SMD-TACT-5.2x5.2x2mm
SW2054: X; SMD-TACT-5.2x5.2x2mm
SW2055: C; SMD-TACT-5.2x5.2x2mm
SW2056: V; SMD-TACT-5.2x5.2x2mm
SW2057: B; SMD-TACT-5.2x5.2x2mm
SW2058: N; SMD-TACT-5.2x5.2x2mm
SW2059: M; SMD-TACT-5.2x5.2x2mm
SW2060: ,; SMD-TACT-5.2x5.2x2mm
SW2061: .; SMD-TACT-5.2x5.2x2mm
SW2062: -; SMD-TACT-5.2x5.2x2mm
SW2063: SHIFT_R; SMD-TACT-5.2x5.2x2mm
SW2064: FN_R; SMD-TACT-5.2x5.2x2mm
SW2065, SW2069: SPACE; SMD-TACT-5.2x5.2x2mm
SW2066: FN_L; SMD-TACT-5.2x5.2x2mm
SW2067: RIGHT; SMD-TACT-5.2x5.2x2mm
SW2068: CTRL; SMD-TACT-5.2x5.2x2mm
U2001, U2002: 4017; SOIC-16_3.9x9.9mm_Pitch1.27mm
U2003: 74HC00; SOIC-14_3.9x8.7mm_Pitch1.27mm

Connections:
+3V3: U2001.16 (VDD), U2002.16 (VDD), U2003.14 (VCC); also elsewhere on the board
/KBD_CLK: U2002.14 (CLK), U2003.4; also elsewhere on the board
/KBD_Q0: D2001.1 (K), D2002.1 (K), D2003.1 (K), D2004.1 (K), D2005.1 (K), D2006.1 (K), D2007.1 (K), D2008.1 (K), D2009.1 (K), D2010.1 (K), D2011.1 (K), D2012.1 (K), D2013.1 (K), D2014.1 (K), D2016.1 (K), D2049.1 (K), D2058.1 (K), RP2001.6 (R3.2); also elsewhere on the board
/KBD_Q1: D2018.1 (K), D2019.1 (K), D2020.1 (K), D2021.1 (K), D2022.1 (K), D2023.1 (K), D2024.1 (K), D2025.1 (K), D2026.1 (K), D2027.1 (K), D2028.1 (K), D2029.1 (K), D2030.1 (K), D2031.1 (K), D2032.1 (K), D2051.1 (K), D2057.1 (K), RP2001.7 (R2.2); also elsewhere on the board
/KBD_Q2: D2015.1 (K), D2034.1 (K), D2035.1 (K), D2036.1 (K), D2037.1 (K), D2038.1 (K), D2039.1 (K), D2040.1 (K), D2041.1 (K), D2042.1 (K), D2043.1 (K), D2044.1 (K), D2045.1 (K), D2046.1 (K), D2047.1 (K), D2048.1 (K), D2050.1 (K), RP2001.8 (R1.2); also elsewhere on the board
/KBD_Q3: D2017.1 (K), D2033.1 (K), D2052.1 (K), D2053.1 (K), D2054.1 (K), D2055.1 (K), D2056.1 (K), D2059.1 (K), D2060.1 (K), D2061.1 (K), D2062.1 (K), D2063.1 (K), D2064.1 (K), D2065.1 (K), D2066.1 (K), D2067.1 (K), D2068.1 (K), RP2001.5 (R4.2); also elsewhere on the board
/KBD_RST: U2003.2; also elsewhere on the board
/Keyboard/COL0: SW2001.1, SW2018.1, SW2035.1, SW2052.1, U2002.1 (Q5)
/Keyboard/COL1: SW2002.1, SW2019.1, SW2036.1, SW2053.1, U2002.2 (Q1)
/Keyboard/COL2: SW2003.1, SW2020.1, SW2037.1, SW2054.1, U2001.15 (Reset), U2002.3 (Q0)
/Keyboard/COL3: SW2004.1, SW2021.1, SW2038.1, SW2055.1, U2002.4 (Q2)
/Keyboard/COL4: SW2005.1, SW2022.1, SW2039.1, SW2056.1, U2002.5 (Q6)
/Keyboard/COL5: SW2006.1, SW2023.1, SW2040.1, SW2057.1, U2002.6 (Q7)
/Keyboard/COL6: SW2007.1, SW2024.1, SW2041.1, SW2058.1, U2002.7 (Q3)
/Keyboard/COL7: SW2008.1, SW2025.1, SW2042.1, SW2059.1, U2002.10 (Q4)
/Keyboard/COL8: SW2009.1, SW2026.1, SW2043.1, SW2060.1, U2002.9 (Q8)
/Keyboard/COL9: SW2010.1, SW2027.1, SW2044.1, SW2061.1, U2001.5 (Q6)
/Keyboard/COL10: SW2011.1, SW2028.1, SW2045.1, SW2062.1, U2001.4 (Q2)
/Keyboard/COL11: SW2012.1, SW2029.1, SW2046.1, SW2063.1, U2001.1 (Q5)
/Keyboard/COL12: SW2013.1, SW2030.1, SW2047.1, SW2064.1, U2001.2 (Q1)
/Keyboard/COL13: SW2014.1, SW2031.1, SW2048.1, SW2065.1, SW2069.1, U2001.6 (Q7)
/Keyboard/COL14: SW2015.1, SW2032.1, SW2049.1, SW2066.1, U2001.7 (Q3)
/Keyboard/COL15: SW2016.1, SW2033.1, SW2050.1, SW2067.1, U2001.10 (Q4)
/Keyboard/COL16: SW2017.1, SW2034.1, SW2051.1, SW2068.1, U2001.9 (Q8)
GND: RP2001.1 (R1.1), RP2001.2 (R2.1), RP2001.3 (R3.1), RP2001.4 (R4.1), U2001.8 (VSS), U2001.13 (CKEN), U2002.8 (VSS), U2003.7 (GND); also elsewhere on the board
unnamed: D2001.2 (A), SW2001.2
unnamed: D2002.2 (A), SW2002.2
unnamed: D2003.2 (A), SW2003.2
unnamed: D2004.2 (A), SW2004.2
unnamed: D2005.2 (A), SW2005.2
unnamed: D2006.2 (A), SW2006.2
unnamed: D2007.2 (A), SW2007.2
unnamed: D2008.2 (A), SW2008.2
unnamed: D2009.2 (A), SW2009.2
unnamed: D2010.2 (A), SW2010.2
unnamed: D2011.2 (A), SW2011.2
unnamed: D2012.2 (A), SW2012.2
unnamed: D2013.2 (A), SW2013.2
unnamed: D2014.2 (A), SW2014.2
unnamed: D2015.2 (A), SW2015.2
unnamed: D2016.2 (A), SW2016.2
unnamed: D2017.2 (A), SW2051.2
unnamed: D2018.2 (A), SW2018.2
unnamed: D2019.2 (A), SW2019.2
unnamed: D2020.2 (A), SW2020.2
unnamed: D2021.2 (A), SW2021.2
unnamed: D2022.2 (A), SW2022.2
unnamed: D2023.2 (A), SW2023.2
unnamed: D2024.2 (A), SW2024.2
unnamed: D2025.2 (A), SW2025.2
unnamed: D2026.2 (A), SW2026.2
unnamed: D2027.2 (A), SW2027.2
unnamed: D2028.2 (A), SW2028.2
unnamed: D2029.2 (A), SW2029.2
unnamed: D2030.2 (A), SW2030.2
unnamed: D2031.2 (A), SW2031.2
unnamed: D2032.2 (A), SW2032.2
unnamed: D2033.2 (A), SW2033.2
unnamed: D2034.2 (A), SW2034.2
unnamed: D2035.2 (A), SW2035.2
unnamed: D2036.2 (A), SW2036.2
unnamed: D2037.2 (A), SW2037.2
unnamed: D2038.2 (A), SW2038.2
unnamed: D2039.2 (A), SW2039.2
unnamed: D2040.2 (A), SW2040.2
unnamed: D2041.2 (A), SW2041.2
unnamed: D2042.2 (A), SW2042.2
unnamed: D2043.2 (A), SW2043.2
unnamed: D2044.2 (A), SW2044.2
unnamed: D2045.2 (A), SW2045.2
unnamed: D2046.2 (A), SW2046.2
unnamed: D2047.2 (A), SW2047.2
unnamed: D2048.2 (A), SW2048.2
unnamed: D2049.2 (A), SW2049.2
unnamed: D2050.2 (A), SW2050.2
unnamed: D2051.2 (A), SW2017.2
unnamed: D2052.2 (A), SW2062.2
unnamed: D2053.2 (A), SW2063.2
unnamed: D2054.2 (A), SW2064.2
unnamed: D2055.2 (A), SW2065.2, SW2069.2
unnamed: D2056.2 (A), SW2066.2
unnamed: D2057.2 (A), SW2067.2
unnamed: D2058.2 (A), SW2068.2
unnamed: D2059.2 (A), SW2052.2
unnamed: D2060.2 (A), SW2053.2
unnamed: D2061.2 (A), SW2054.2
unnamed: D2062.2 (A), SW2055.2
unnamed: D2063.2 (A), SW2056.2
unnamed: D2064.2 (A), SW2057.2
unnamed: D2065.2 (A), SW2058.2
unnamed: D2066.2 (A), SW2059.2
unnamed: D2067.2 (A), SW2060.2
unnamed: D2068.2 (A), SW2061.2
unnamed: R2001.1, U2003.6
unnamed: R2001.2, U2003.9, U2003.10
unnamed: U2001.11 (Q9), U2003.12, U2003.13
unnamed: U2001.14 (CLK), U2003.8
unnamed: U2002.11 (Q9), U2002.13 (CKEN), U2003.5
unnamed: U2002.15 (Reset), U2003.3
unnamed: U2003.1, U2003.11

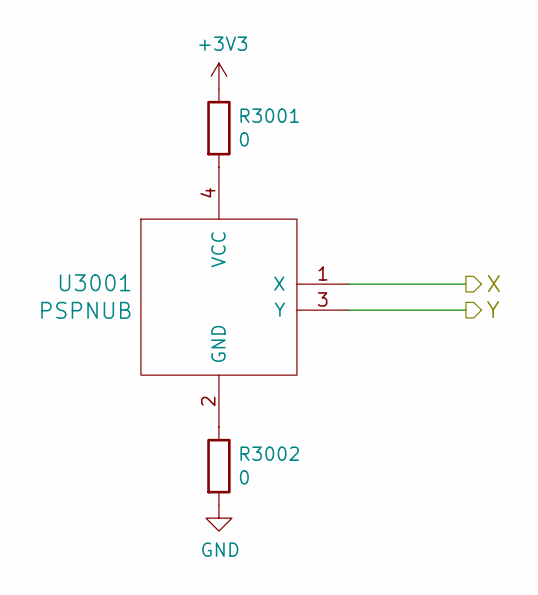
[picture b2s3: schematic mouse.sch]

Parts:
R3001, R3002: 0; R_1206
U3001: PSPNUB

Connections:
+3V3: R3001.1; also elsewhere on the board
/MOUSE_X: U3001.1 (X); also elsewhere on the board
/MOUSE_Y: U3001.3 (Y); also elsewhere on the board
GND: R3002.2; also elsewhere on the board
unnamed: R3001.2, U3001.4 (VCC)
unnamed: R3002.1, U3001.2 (GND)

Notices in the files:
hdl/trollbook.qsf:
Copyright (C) 1991-2009 Altera Corporation
